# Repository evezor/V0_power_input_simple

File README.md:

# power_input_simple
*please note this board is has been deprecated.

This board uses the Evezor Stamp STMF405 MCU

source: https://github.com/evezor/Evezor-Stamp-STMF405

Simple power input for Evezor Edge network boards

Evezor® and all associated marks, logos, and designs are registered trademarks and protected by copyright. Unauthorized use or reproduction of these trademarks and copyrighted materials is strictly prohibited.

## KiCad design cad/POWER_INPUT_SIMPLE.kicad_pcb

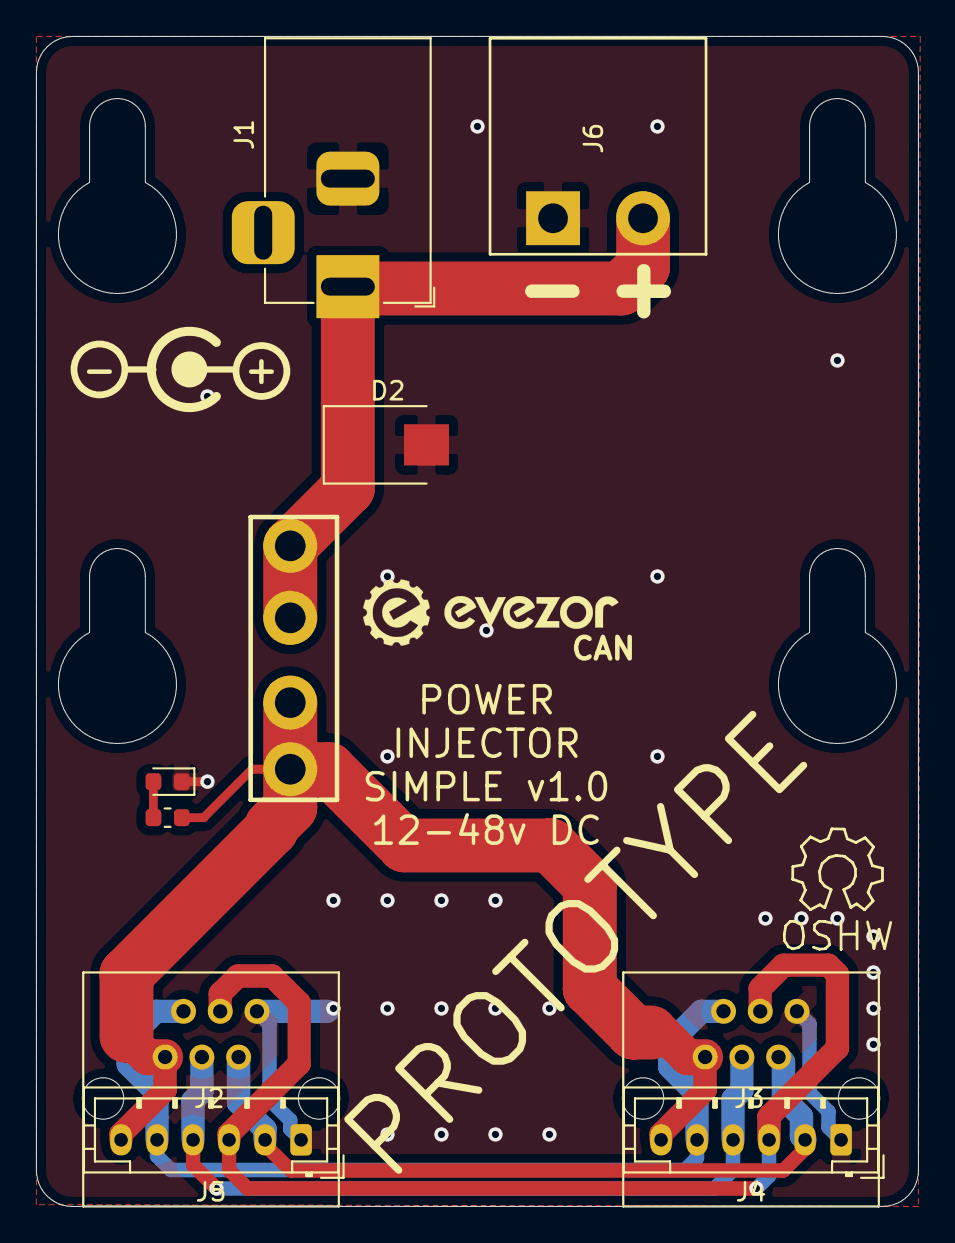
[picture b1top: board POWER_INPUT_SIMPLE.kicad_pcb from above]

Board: 2 copper layers, 49.0 x 65.0 mm, 10 parts (0 on the bottom side), 8 nets.

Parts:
D1: LED; LED_0603_1608Metric
D2: Diode; D_SMB
F1: Fuse; FUSE_BK-6013-ND
J1: Barrel_Jack; BarrelJack_Horizontal
J2, J3: RJ11; RJ11_C189747_Horizontal
J4, J5: PH; JST_PH_B6B-PH-K_1x06_P2.00mm_Vertical
J6: Screw_Terminal_01x02; CONN_ON_SHORE_2x_15A
R1: 4.7k; R_0603_1608Metric

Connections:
+24V: D2.1, F1.2, J1.1, J6.1
/CAN_H: J2.3, J3.3, J4.3, J5.3
/CAN_L: J2.4, J3.4, J4.4, J5.4
/FD_H: J2.2, J3.2, J4.2, J5.2
/FD_L: J2.5, J3.5, J4.5, J5.5
/FUSED: F1.1, J2.6, J3.6, J4.6, J5.6, R1.2
GND: D1.1, D2.2, J1.2, J2.1, J3.1, J4.1, J5.1, J6.2
unnamed: D1.2, R1.1

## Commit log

2021-04-21 add cad files
2023-09-11 Create LICENSE
2023-09-11 add pics
